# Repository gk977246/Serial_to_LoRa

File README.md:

# Serial_to_LoRa

Modified to work with Ebyte E77 and Rak3172

Radiohead library has only support for Wio E5 - I changed  that

Rak3172: works
EbyteE77: has no variant in stm32duino compile as WioE5

check the serial pins in the variant of the board - Serial for debugging HardwareSerial for Gps

Transmit and receive programs for Adafruit Feather M0 LoRa module to transmit one way data over LoRa. I have used these routines previously with a U-blox C94-M8P evaluation kit to send RTK correction data (RTCM3) from base GPS to rover GPS for an autonomous lawn mower based on Ardupilot running on a Pixhawk. I have upgraded to U-blox C099-F9P eval boards and Ardusimple SimpleRTK2B boards (Either will work.)

I discovered, on July 1, 2020, that I could run the LoRa modules at a bandwidth of 62.5kbps instead of 125kbps. I made that change which theoretically will give more range. In testing, I did not notice a difference.

**Modifications to both Rover and Base Feather M0 (for my situation, at least):**
I powered the feather via the Vbat pin from another board (host) in my system (the GPS for instance). The board has an MCP73881/2 LiPo charge controller connected to Vbat. It is designed to charge a battery connected to Vbat when power is present on the USB port. I have had a couple of Feather failures which I believe were caused by the Feather back-powering the host board when I had a USB cable connected to the Feather (for programming) but I did NOT power up the host board. I am not completely sure, but to keep this from happening, I inserted a diode, such as a 1N4007 in the +5V signal from the host.

**Using Feather M0 Lora with Ublox C099-F9P evaluation boards:**

  Rover:
  I am powering the Feather board with its Vbat input from the 5V Servo power rail on the Pixhawk through a diode.

  Base:
  I am powering the Feather Vbat from the 5Vout pin of the C099-F9P board through a diode.

**Using Feather M0 Lora with a Ublox C94-M8P evaluation kit:**

  Rover:
  I am powering the Feather board with its Vbat input from the 5V Servo power rail on the Pixhawk through a diode.

  Base:
  The C94-M8P can be powered with a 3.7V – 20V supply. I am powering the C94-M8P and the Feather from a 5V wall wart power supply.

  You must disable the onboard radio modem on the C94-M8P boards as well. Refer to the documentation for the board on how to do that.

Kenny Trussell
http://kenny.trussell.biz

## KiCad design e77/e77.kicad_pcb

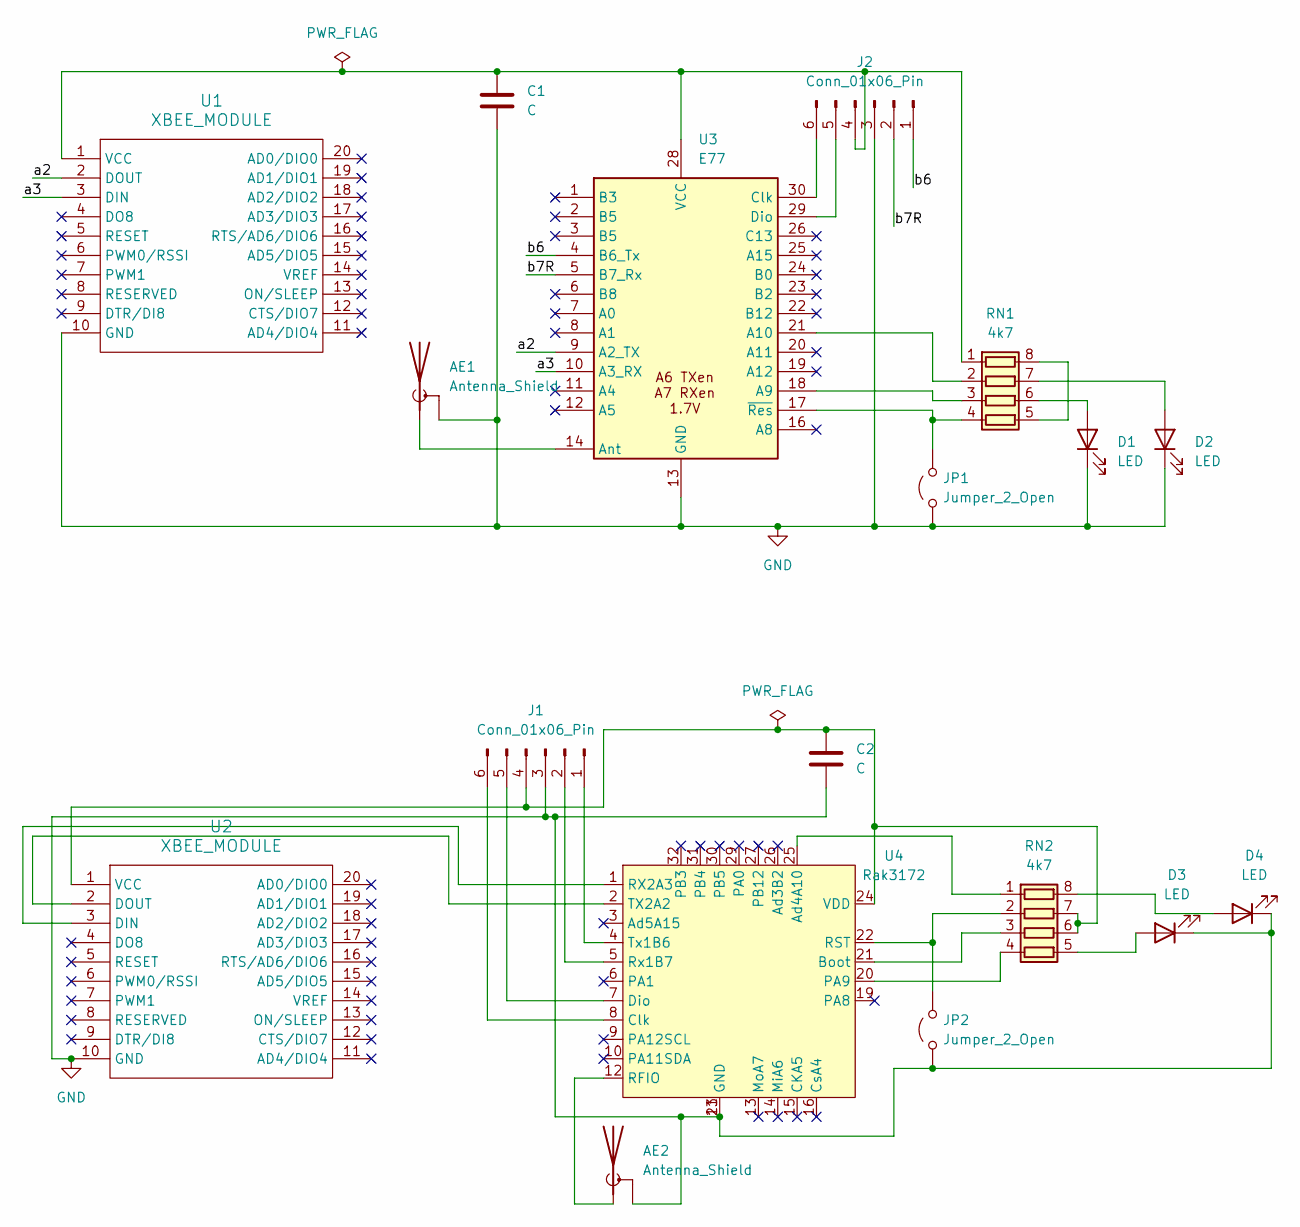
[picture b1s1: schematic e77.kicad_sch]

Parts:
AE1, AE2: Antenna_Shield; SMA_Samtec_SMA-J-P-X-ST-EM1_EdgeMount
C1, C2: C; C_0603_1608Metric
D1, D2, D3, D4: LED; LED_0603_1608Metric
J1, J2: Conn_01x06_Pin; PinHeader_1x06_P2.54mm_Vertical
JP1, JP2: Jumper_2_Open; SolderJumper-2_P1.3mm_Open_RoundedPad1.0x1.5mm
RN1, RN2: 4k7; R_Array_Convex_4x0603
U1, U2: XBEE_MODULE; XBee-KiCad-Rookie
U3: E77; EbyteE77
U4: Rak3172; rak3172

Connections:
/a2: U1.2 (DOUT), U3.9 (A2_TX)
/a3: U1.3 (DIN), U3.10 (A3_RX)
/b6: J2.1, U3.4 (B6_Tx)
/b7R: J2.2, U3.5 (B7_Rx)
GND: AE1.2 (Shield), AE2.2 (Shield), C1.2, C2.2, D1.1 (K), D2.1 (K), D3.1 (K), D4.1 (K), J1.3, J2.3, JP1.1 (A), JP2.1 (A), U1.10 (GND), U2.10 (GND), U3.13 (GND), U3.15 (GND), U3.27 (GND), U4.11 (GND), U4.17 (GND), U4.18 (GND), U4.23 (GND), U4.28 (GND)
unnamed: AE1.1 (A), U3.14 (Ant)
unnamed: AE2.1 (A), U4.12 (RFIO)
unnamed: D1.2 (A), RN1.6 (R3.2)
unnamed: D2.2 (A), RN1.7 (R2.2)
unnamed: D3.2 (A), RN2.5 (R4.2)
unnamed: D4.2 (A), RN2.8 (R1.2)
unnamed: J1.1, U4.4 (Tx1B6)
unnamed: J1.2, U4.5 (Rx1B7)
unnamed: C2.1, J1.4, RN2.6 (R3.2), RN2.7 (R2.2), U2.1 (VCC), U4.24 (VDD)
unnamed: J1.5, U4.7 (Dio)
unnamed: J1.6, U4.8 (Clk)
unnamed: C1.1, J2.4, RN1.1 (R1.1), U1.1 (VCC), U3.28 (VCC)
unnamed: J2.5, U3.29 (Dio)
unnamed: J2.6, U3.30 (Clk)
unnamed: JP1.2 (B), RN1.4 (R4.1), U3.17 (~Res)
unnamed: JP2.2 (B), RN2.2 (R2.1), U4.22 (RST)
unnamed: RN1.5 (R4.2), RN1.8 (R1.2)
unnamed: RN1.2 (R2.1), U3.21 (A10)
unnamed: RN1.3 (R3.1), U3.18 (A9)
unnamed: RN2.1 (R1.1), U4.25 (Ad4A10)
unnamed: RN2.3 (R3.1), U4.21 (Boot)
unnamed: RN2.4 (R4.1), U4.20 (PA9)
unnamed: U2.3 (DIN), U4.1 (RX2A3)
unnamed: U2.2 (DOUT), U4.2 (TX2A2)

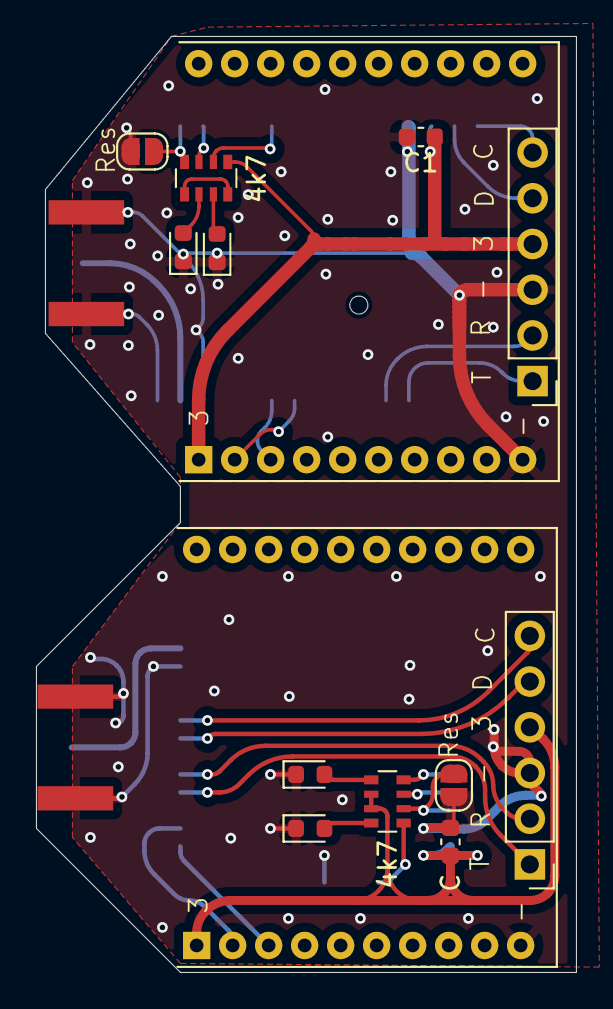
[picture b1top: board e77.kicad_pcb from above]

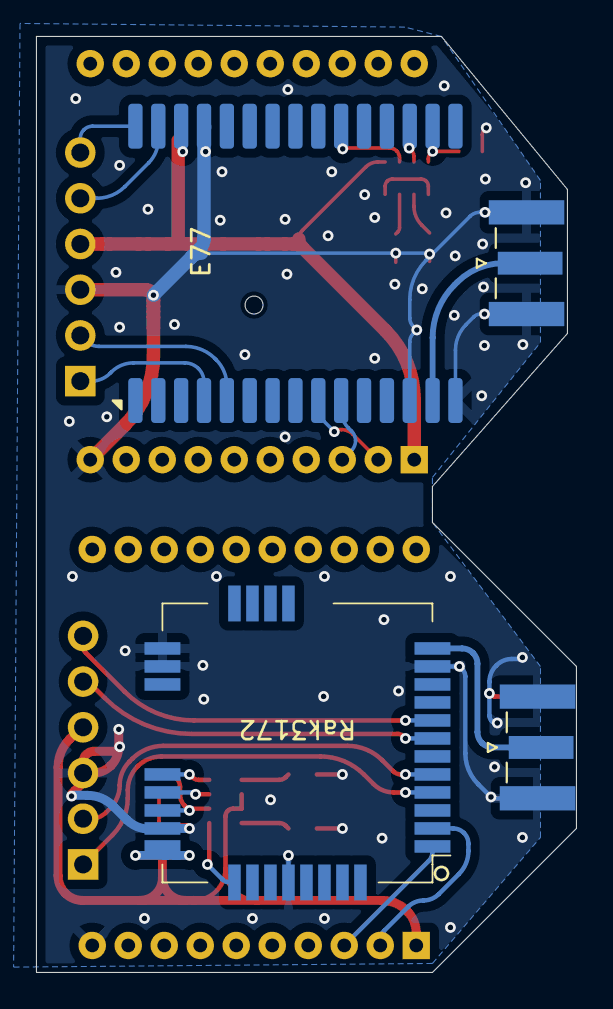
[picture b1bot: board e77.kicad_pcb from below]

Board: 2 copper layers, 30.0 x 52.0 mm, 18 parts (4 on the bottom side), 29 nets.

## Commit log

2025-09-09 Modified to work with Stm32Wl
2025-09-09 add Radiohead_Lib
2025-09-09 build files
2025-09-10 rename build
